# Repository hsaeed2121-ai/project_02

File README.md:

# project_02

# For EMG circuit for my senior design project
# Takes two electrode inputs from across muscle (meant for upper extremity) and outputs a code that needs to be processed by a python script to send a signal to motor actuators (to replicate intended motion from EMG).

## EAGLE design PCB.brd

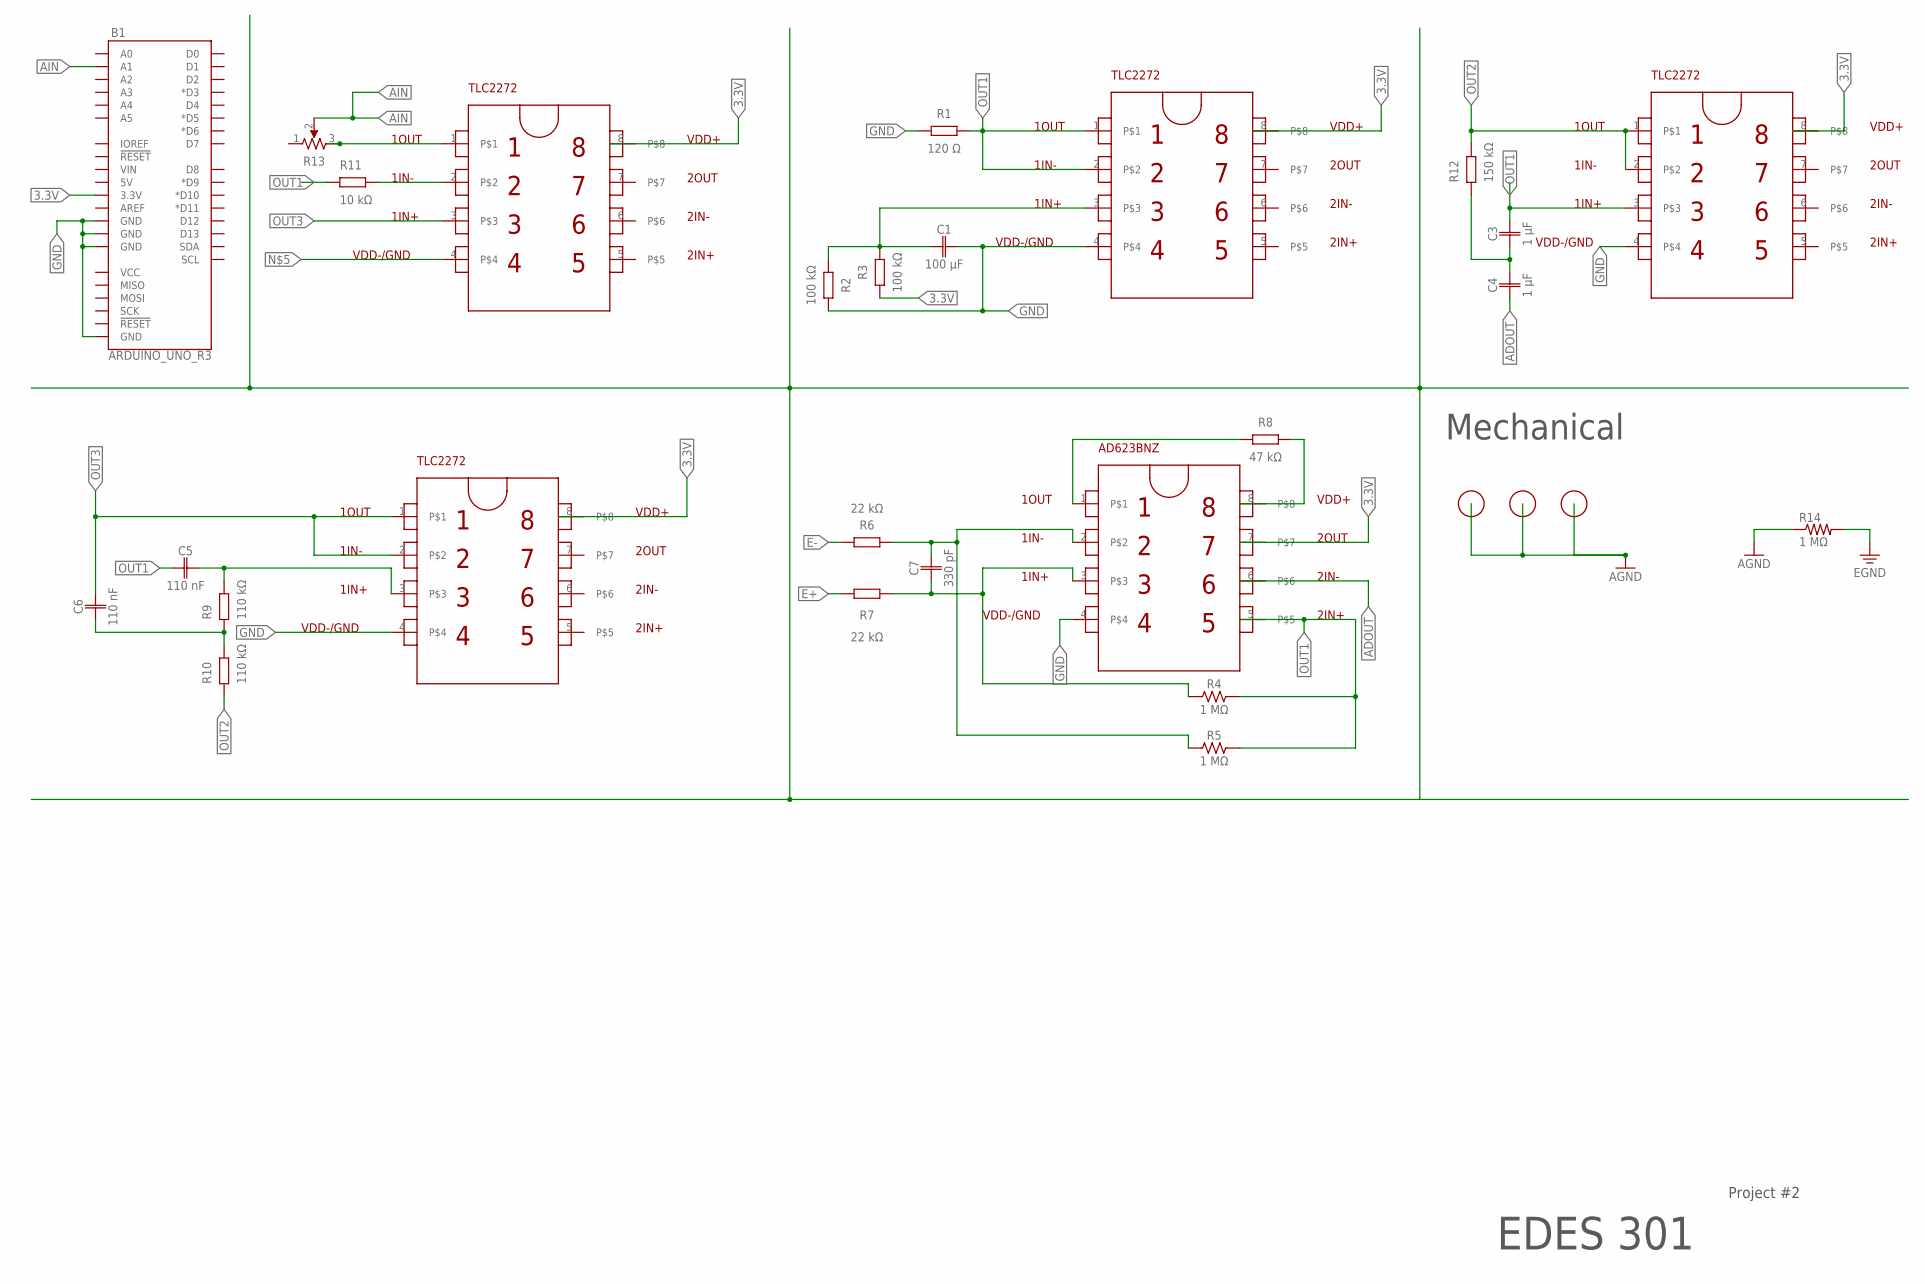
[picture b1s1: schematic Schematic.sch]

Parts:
B1: ARDUINO_UNO_R3; ARDUINO_R3
C1: 100 μF; CAPC1005X60
C3, C4: 1 μF; CAPC1005X60
C5, C6: 110 nF; CAPC1005X60
C7: 330 pF; CAPC1005X60
R1: 120 Ω; RESC1005X40
R2, R3: 100 kΩ; RESC1005X40
R4, R5, R14: 1 MΩ; RESC1005X40
R6, R7: 22 kΩ; RESC1005X40
R8: 47 kΩ; RESC1005X40
R13: PTV09A-40-B20220F; PTV09A-X
U$1: AD623BNZDIP8; DIP8
U$2, U$3, U$4, U$5: TLC2272; DIP8
U$6, U$7, U$9: FIDUCIAL; FIDUCIAL_1MM

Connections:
3.3V: B1.3.3V, R3.1, U$1.7, U$2.8, U$3.8, U$5.8
ADOUT: C4.1, U$1.6
AIN: B1.A1, R13.2
E+: R7.1
E-: R6.1
EGND: R14.2
GND: B1.GND@1 (GND), B1.GND@2 (GND), B1.GND@3 (GND), B1.GND@4 (GND), C1.2, R1.1, R2.2, U$1.4, U$2.4, U$3.4, U$5.4
unnamed: C3.1, C4.2
unnamed: C1.1, R2.1, R3.2, U$5.3
unnamed: C5.2, U$3.3
unnamed: C7.2, R5.1, R6.2, U$1.2
unnamed: C7.1, R4.1, R7.2, U$1.3
unnamed: R8.2, U$1.8
unnamed: R8.1, U$1.1
unnamed: R13.3, U$4.1
OUT1: C3.2, C5.1, R1.2, R4.2, R5.2, U$1.5, U$2.3, U$5.1, U$5.2
OUT2: U$2.1, U$2.2
OUT3: C6.2, U$3.1, U$3.2, U$4.3

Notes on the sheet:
Mechanical
EDES 301
Project #2

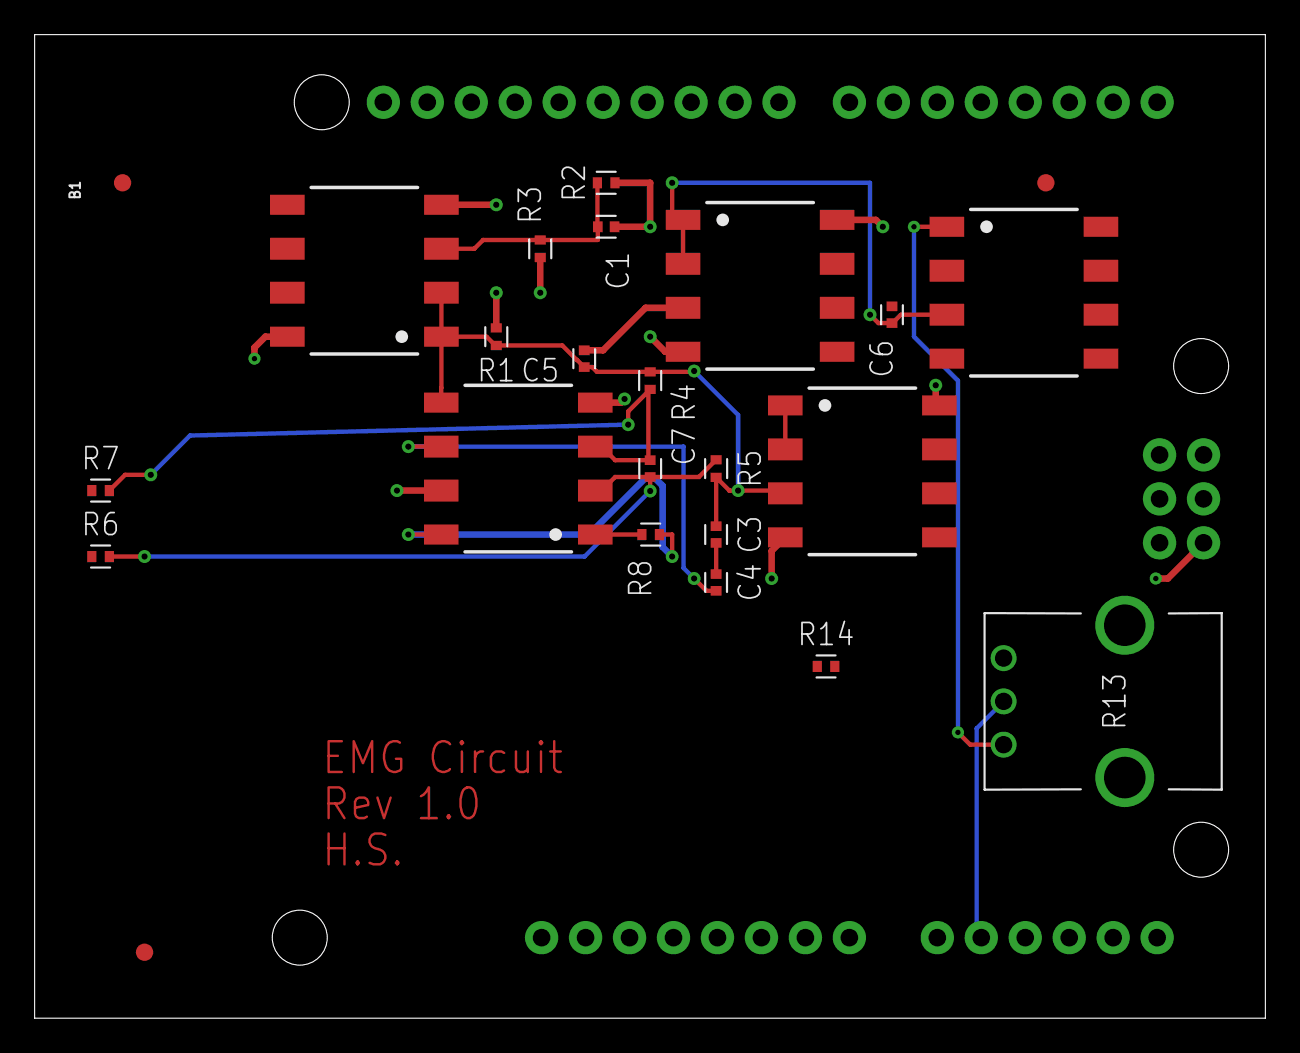
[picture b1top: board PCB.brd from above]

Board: 4 copper layers, 71.1 x 56.8 mm, 25 parts (0 on the bottom side), 15 nets.
